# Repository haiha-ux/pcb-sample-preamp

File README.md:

# 2-channel phantom-powered mic preamp, KiCad sample

Owner: Hai (GitHub `haiha-ux`). This is a test and portfolio project, not client work.

A KiCad 10.0.6 project: schematic and a 2-layer 100 × 78 mm PCB, with ERC/DRC reports, fab outputs and renders. The audio signal path is routed by hand. Only power, the phantom feed and ground are autorouted. Every file is generated by the scripts in `tools/`, so the whole design can be rebuilt from scratch.

| Top copper | Bottom copper |
|---|---|
|  |  |

Schematic: [mic_preamp_2ch_schematic.pdf](mic_preamp_2ch_schematic.pdf)

## What is on the board

Per channel (×2):

| Block | Parts | Source |
|---|---|---|
| Input | Neutrik NC3FAH1 female XLR, horizontal (pin 1 GND, 2 hot, 3 cold) | — |
| Phantom feed | Per leg, **2 × 3.40 kΩ 0.1 % thin film 1206 in series (6.80 kΩ)**; 3-pin jumper ON (1-2 → +48 V) / OFF (2-3 → 47 kΩ to GND) | INA163 datasheet Fig. 5 (R1, R2, R3) |
| DC block | 2 × 47 µF 63 V **bi-polar** electrolytic | Fig. 5 note (1): non-polar required when phantom can be switched off |
| Input protection | BAV99 dual diode per leg, clamping to ±15 V | Fig. 5 text ("four diodes to the supplies") |
| Bias return | 2 × 2.2 kΩ **0.1 %** to GND | Fig. 5 (R4, R5) |
| Series resistor | 10 Ω 0.1 % per leg, between the clamp node and the IC input | design choice, see below |
| Preamp | TI **INA163UA** (SOIC-14), G = 1 + 6000/RG, RG = 60.4 Ω → G = 100.3 (40.0 dB) | gain equation and table, datasheet p. 6 |
| Decoupling | 100 nF X7R on each rail, right at the IC pins | Fig. 1 ("0.1 µF near the device pins") |

Shared: ±15 V header J3 with 10 µF on each rail and SMAJ16A TVS rail clamps (D21/D22);
+48 V header J4 with 47 µF/100 V + 100 nF; line-out header J5 (OUT1/GND/OUT2/GND); 4 × M3 holes.

I used the TI SBOS177D datasheet (INA163). The pin-out is from p. 2, the gain from p. 6 and the application circuit from Fig. 5 on p. 8. I rendered each figure and compared it to the schematic node by node (see the v2 correction below for why).

## Layout (v2)

The IC is rotated 90°. Input pins 4/5 face the XLR and output pins 8/9 face the connectors on the far edge, so the output never runs near the input, as the datasheet asks on p. 6.

The hot and cold legs are routed by hand as a symmetric pair. They run 11.5 mm apart, each straight through its DC-block capacitor and 10 Ω resistor. Clamp diodes and bias resistors branch off to the outside of each leg, and the two legs converge onto pins 4/5 at 45°. The measured copper length per leg after the capacitors is IN±_PROT 16.30 / 16.30 mm and IN± 11.72 / 11.72 mm, with 0 vias on each leg. Between the XLR and the capacitors the lengths differ: hot 24.8 mm, cold 19.5 mm, including the phantom stubs. The XLR pin order is mirrored relative to the IC pin order, so the legs must cross once. They cross here using the through-hole pads (hot on B.Cu), which needs no via.

The RG loop is short: R8/R18 sit next to the IC end, with a 9.1 mm loop (RG1A/RG1B).

Decoupling caps are placed on the V+ and V− pins, with a GND via at each cap. The Ref pin (pin 10) goes through a via straight into the GND pour, with no thermal relief. Datasheet p. 6 says even a few ohms in series with Ref hurts CMRR.

Freerouting 2.4.1 routes the ±15 V rails, the +48 V/phantom feed and GND. The 98 hand-routed tracks and vias are locked and exported as `fix`, so the router cannot move them. GND is poured on both layers, with 103 stitching vias.

## Outputs

| File | What |
|---|---|
| `mic_preamp_2ch.kicad_pro/.kicad_sch/.kicad_pcb/.kicad_dru` | KiCad project, including custom DRC rules |
| `lib/preamp.kicad_sym` | INA163UA symbol (not in the stock KiCad library) |
| `mic_preamp_2ch_schematic.pdf` | schematic, A3 |
| `reports/erc_report.rpt/.json` | raw `kicad-cli sch erc --severity-all` output |
| `reports/drc_report.rpt/.json` | raw `kicad-cli pcb drc --severity-all --schematic-parity` output |
| `fab/gerber/` + `fab/mic_preamp_2ch-gerber.zip` | Gerber X2 (9 layers), Excellon PTH/NPTH, drill maps, job file |
| `fab/mic_preamp_2ch-BOM.csv` | BOM with manufacturer, MPN, LCSC number |
| `fab/mic_preamp_2ch-CPL.csv` | pick-and-place (SMD only) |
| `renders/` | 3D top / bottom / iso, plus 2D copper views of top and bottom |

## Check results (final board)

ERC gives 0 errors and 0 warnings. DRC gives 0 errors, 0 unconnected and 0 schematic-parity issues, plus 4 warnings, all waived (see below).

The `kicad-cli` netlist is compared pin by pin with the intended net table (`tools/check_netlist.py`) and matches 100%. The check has a built-in sabotage case: moving one pin to another net must make it fail.

To confirm the 48 V clearance rule is applied, I raised it from 0.6 mm to 5 mm on a copy of the board. DRC then reported 301 "P48 creepage" violations, so the rule really matches the 48 V nets and does not pass trivially.

I counted the hits in the Excellon drill files (167 PTH + 8 NPTH), and they match the pads and vias on the board.

A separate reviewer re-ran the checks on another machine with KiCad 10.0.8 and the official libraries: ERC 0, DRC 0 errors, 0 unconnected, 0 parity issues, the same 4 XLR silk warnings, and no footprint differs from the library.

### Waived DRC items

| Item | Count | Reason |
|---|---|---|
| `silk_edge_clearance`, J1/J2 | 4 | The NC3FAH1 front flange sits in front of the panel line, which the footprint marks on Dwgs.User at x = 12.7 mm. The board edge is placed on that panel line, so the flange outline overhangs the board by design. |

### Design-rule decisions

These change what "0 errors" means.

- The board minimum track width is 0.15 mm (the KiCad default is 0.2 mm). This lets the autorouter narrow tracks at SOIC pads. JLCPCB and PCBWay handle 0.1 mm.
- ±15 V tracks are at least 0.4 mm. Inside the IC and decoupling-cap courtyards they may narrow to 0.3 mm. Those are local stubs carrying a few mA. This is the `Power neck-down` rule in the `.kicad_dru` file.
- All nets that can carry 48 V have at least 0.6 mm clearance: +48V, PH1/2, P1H/P1C/P2H/P2C, XLRx_HOT, XLRx_COLD and P48OFF1/2. The value is IPC-2221B table 6-1, column B2 (external, uncoated, 31-150 V). I did not count solder mask as a coating, which is the conservative choice.
- GND pads of J3/J4/J5 are solid, with no thermal relief. `tools/build_pcb.py::fix_starved` applies the same treatment to any GND pad that DRC reports as `starved_thermal`. There are none on the final board.

## v2 changes (after independent review of v1, commit efc1e58)

First, a correction. v1 had 47 Ω in series with each input, and the README said it came from datasheet Fig. 2. That was wrong. Fig. 2 shows 47 Ω in parallel with 1.2 µH, and I had read only the extracted text of the page, not the figure. Two 47 Ω resistors in series add √(4kT·94 Ω) ≈ 1.25 nV/√Hz, which is more than the INA163's own 1 nV/√Hz. v2 uses 10 Ω 0.1 % per leg. It still shares fault current with the IC's internal input clamps (abs-max 10 mA) and adds 0.57 nV/√Hz for both legs. The total is about 1.15 nV/√Hz, or +1.2 dB of noise.

Second, the parts are now matched for CMRR. The phantom feed resistors are 0.1 % thin film. A 6.81 kΩ part of that grade exists only in 1206 (0.25 W), but a shorted mic line puts 0.34 W into one leg. So each leg is 2 × 3.40 kΩ in series: 6.80 kΩ, 0.17 W per part. The bias resistors are 0.1 % too.

Third, the signal path is routed by hand (see Layout). In v1 everything was autorouted, so the hot and cold legs were not paired and there was a long detour.

Two items from the review are not done and remain known limitations:

- EMI filtering and AES48 grounding at the XLR. There are no small caps from pins 2/3 to the shell, and the shell is not taken to a separate chassis point. With the NC3FAH1 the shell is tied to pin 1 inside the connector. Separating them needs the NC3FAH2, which has its own ground contact.
- The DC servo of Fig. 5 (OPA134) is not fitted, so the output is DC-coupled. Estimated DC offset at G = 100, from datasheet values, is typically about 7 mV (Vos) plus 22 mV (Ios × 2.2 kΩ), and worst case about 30 mV plus 220 mV. The next stage must be AC-coupled.

## Deviations from the brief and datasheet

Please review these.

1. The phantom "switch" is a 3-pin jumper header (Molex 22-28-4030, 500 V) plus a shunt, not a slide switch. Every small PCB slide switch I checked has a DC rating below the 48 V ±4 V of IEC 61938:
   - C&K OS102011: 12 VDC
   - Würth 450301014042: 12 VDC
   - E-Switch EG1271: 30 V
   - E-Switch EG1224: 15 VDC
   - C&K 7101 toggle: 28 VDC

   The header doubles as the connection point for a panel-mount switch. Its OFF position discharges the node through 47 kΩ, the same as R3 in datasheet Fig. 5.
2. Gain is fixed at 40 dB, although the brief said "gain set by one resistor". Change R8/R18 using the RG table on p. 6.
3. The C1/C2 type (Nichicon UVP1J470MPD) is marked "Not For New Designs" on DigiKey. Cornell Dubilier 476BPS063M (active) is listed as the alternative. Neither is stocked at LCSC, so the board is not fully JLC-assemblable as is.
4. BAV99 is used instead of 1N4148, with the same function in a smaller package (Nexperia BAV99: 100 V, 4 A surge per the LCSC listing).

## Open questions

- XLR footprint. I used the stock KiCad `Jack_XLR_Neutrik_NC3FAH1_Horizontal`. The Neutrik/LCSC drawing download was blocked, so I did not check its hole sizes and peg positions against the manufacturer drawing myself. There is also no 3D model for it in the KiCad library.
- P48 hot-plug. A shorted XLR line dumps the 48 V charge of C1/C2 through the BAV99 diodes into the rails. I added the SMAJ16A rail clamps for that, but there is no surge simulation or test. The INA163 datasheet does not cover this case.
- Creepage value. I chose the conservative 0.6 mm. If solder mask is counted as a coating (IPC-2221B A6/B4), about 0.13 mm would be enough.
- Ground split by the rails and OUT1. The autorouted ±15 V rails and the OUT1 track run partly on B.Cu, under the channel-1 input area. They cut the bottom GND pour into a long slot (reviewer note). The F.Cu pour and the stitching vias carry the return current, but I have not analysed this. Planned for v3: move these tracks to the board edge or route them tighter, switch to the NC3FAH2 connector and add EMI filtering at the XLR.
- Footprint height for C1/C2. The bi-polar caps use `C_Radial_D10.0mm_H20.0mm_P5.00mm`, while the real part is 17.5 mm tall. The 2D land pattern is the same and only the 3D height is off.
- There is no SPICE or noise simulation. Gain, noise and offset come from the datasheet equations only.

## Tool chain and how to rebuild

The tool is KiCad 10.0.6. The schematic is written only through the Konnect MCP server (`tools/kcall.py` drives it over stdio), and the `.kicad_sch` file is never edited as text. The PCB is built with KiCad's own `pcbnew` Python API, including the hand-routed signal paths. The rest is routed with Freerouting 2.4.1 on Temurin JRE 25. The native `freerouting-cli` 2.5.0 crashed with a GraalVM serialization error. Parts and MPNs come from the JLCPCB/LCSC parts database (local copy), plus DigiKey lookups for the bi-polar caps and the switch ratings.

To rebuild:

```bash
python tools/build_schematic.py      # move the old .kicad_sch out of the way first
python tools/check_netlist.py
"C:/Program Files/KiCad/10.0/bin/python.exe" tools/build_pcb.py all   # with KiCad closed
bash tools/export_outputs.sh
```

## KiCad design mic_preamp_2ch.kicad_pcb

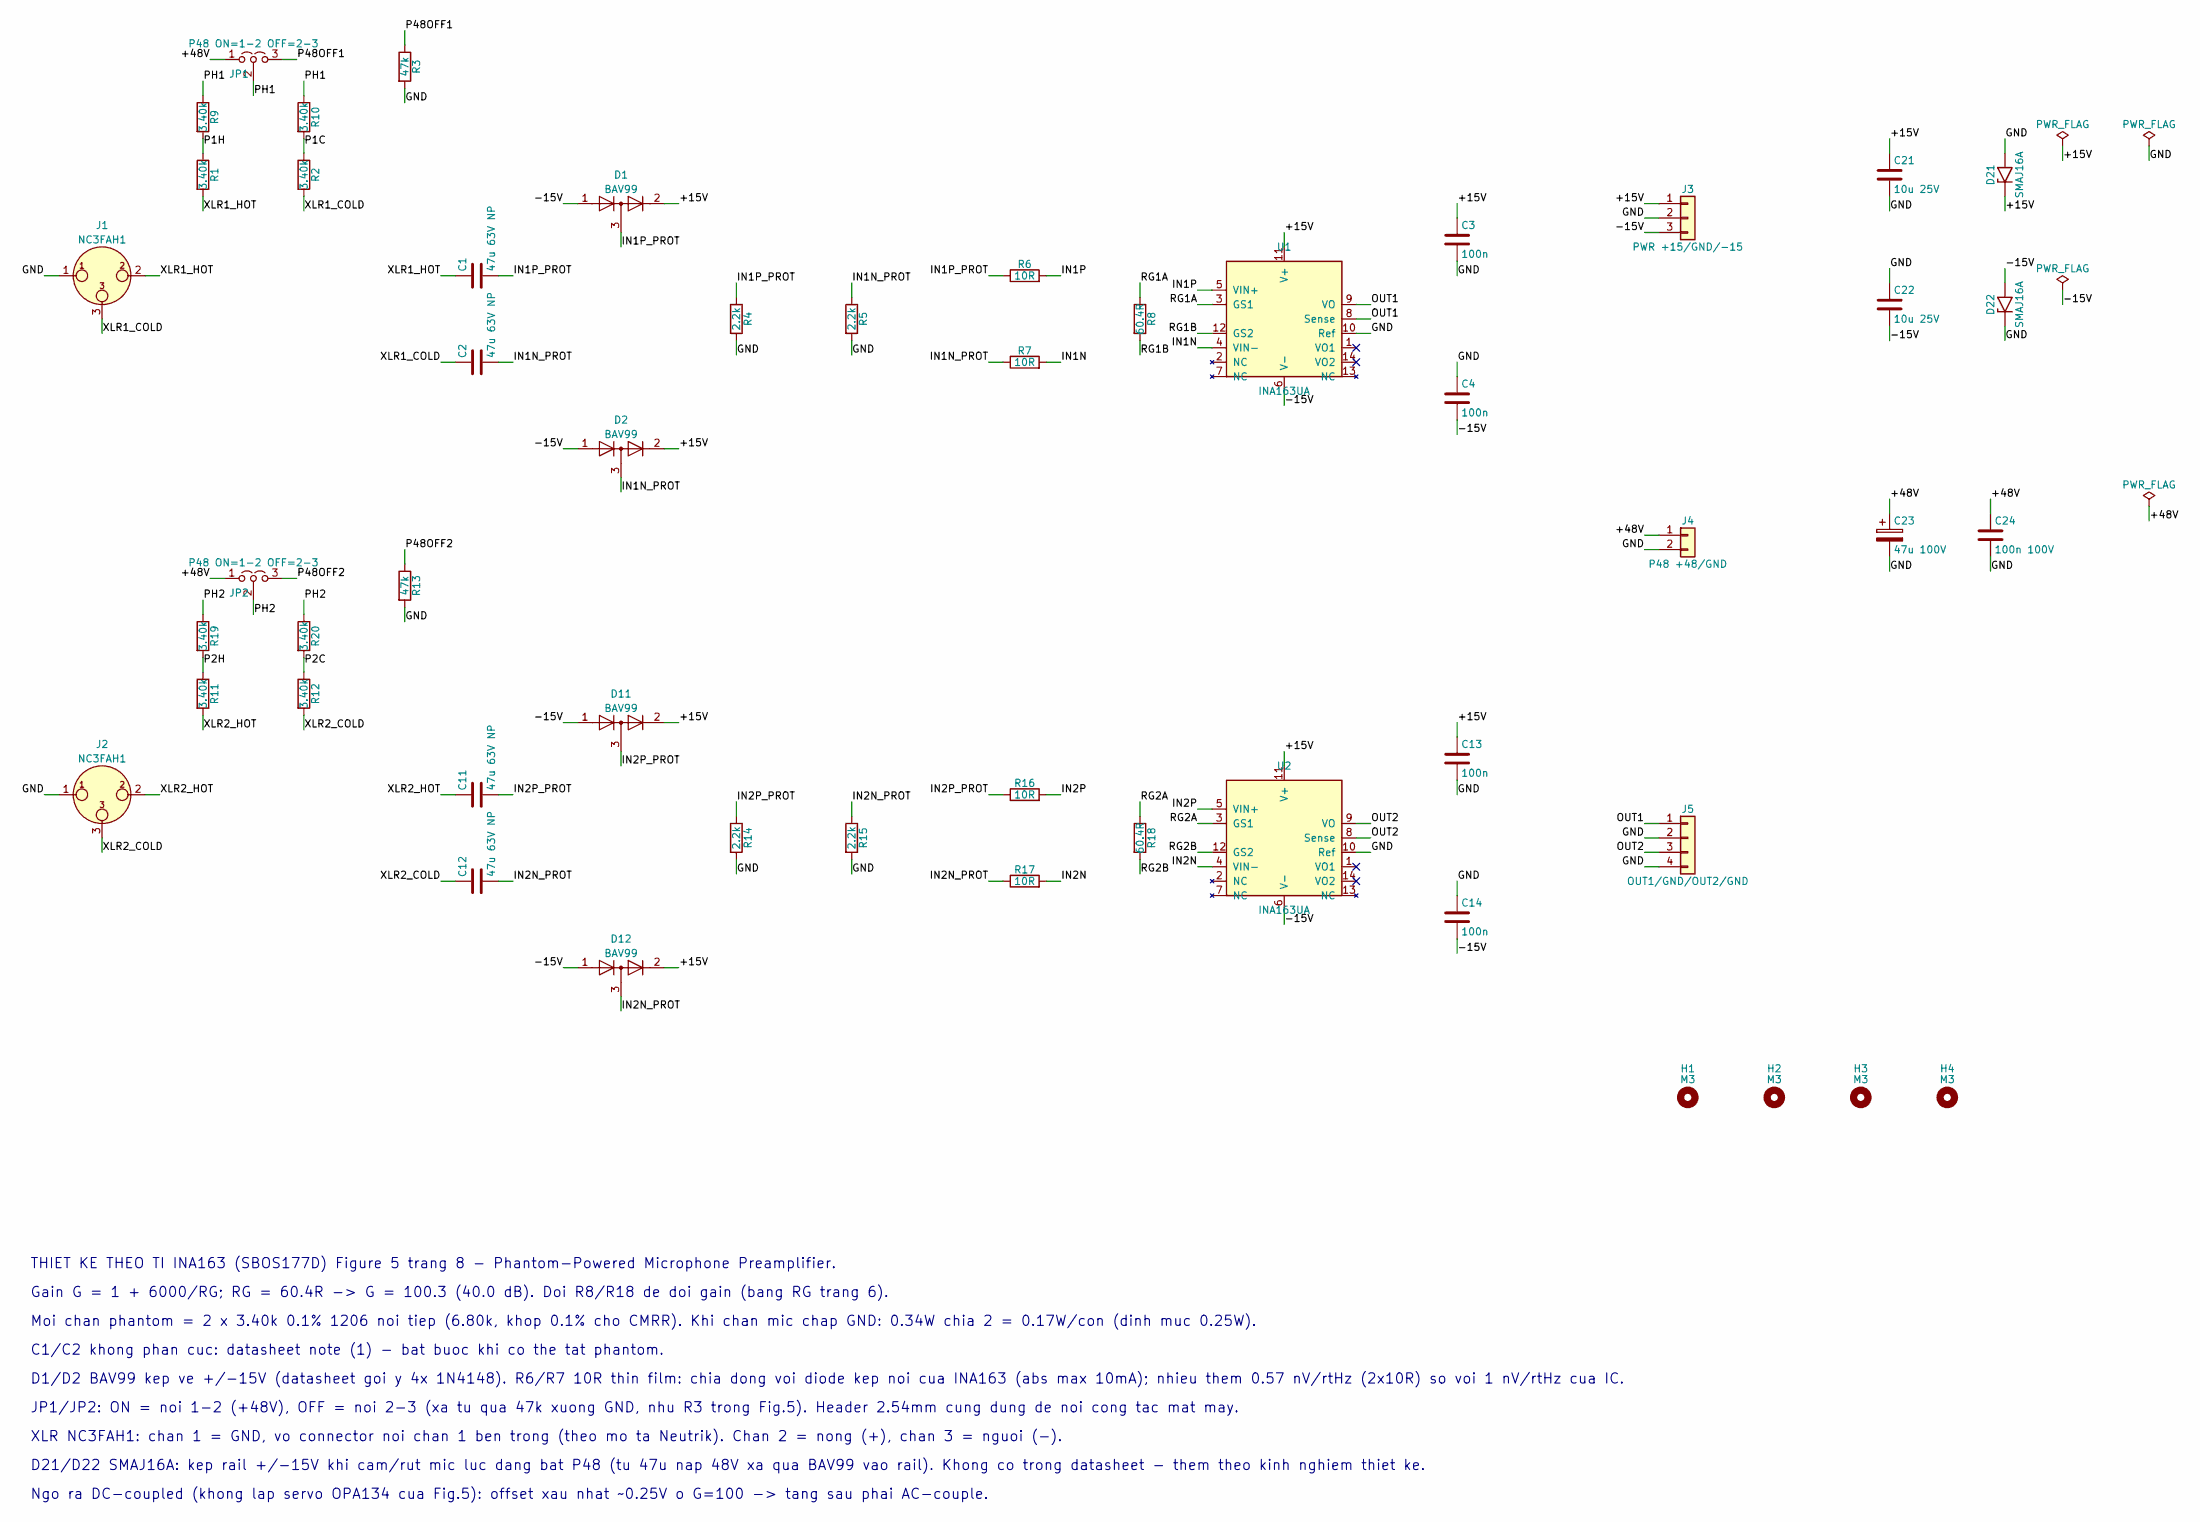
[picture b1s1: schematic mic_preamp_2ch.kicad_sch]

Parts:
C1, C2, C11, C12: 47u 63V NP; C_Radial_D10.0mm_H20.0mm_P5.00mm; MPN UVP1J470MPD; LCSC not stocked (DigiKey)
C3, C4, C13, C14: 100n; C_0805_2012Metric; MPN CC0805KRX7R9BB104; LCSC C49678
C21, C22: 10u 25V; C_1206_3216Metric; MPN CL31B106KAHNNNE; LCSC C14860
C23: 47u 100V; CP_Radial_D8.0mm_P3.50mm; MPN 4701010812R00; LCSC C5373423
C24: 100n 100V; C_0805_2012Metric; MPN CL21B104KCFNNNE; LCSC C28233
D1, D2, D11, D12: BAV99; SOT-23; MPN BAV99,215; LCSC C2500
D21, D22: SMAJ16A; D_SMA; MPN SMAJ16A; LCSC C74561
H1, H2, H3, H4: M3; MountingHole_3.2mm_M3
J1, J2: NC3FAH1; Jack_XLR_Neutrik_NC3FAH1_Horizontal; MPN NC3FAH1; LCSC C368476
J3: PWR +15/GND/-15; PinHeader_1x03_P2.54mm_Vertical; MPN 22284030; LCSC C587036
J4: P48 +48/GND; PinHeader_1x02_P2.54mm_Vertical; MPN 22284020; LCSC C234182
J5: OUT1/GND/OUT2/GND; PinHeader_1x04_P2.54mm_Vertical; MPN 22284040; LCSC C587039
JP1, JP2: P48 ON=1-2 OFF=2-3; PinHeader_1x03_P2.54mm_Vertical; MPN 22284030; LCSC C587036
R1, R2, R9, R10, R11, R12, R19, R20: 3.40k; R_1206_3216Metric; MPN RT1206BRD073K4L; LCSC C870711
R3, R13: 47k; R_0805_2012Metric; MPN 0805W8F4702T5E; LCSC C17713
R4, R5, R14, R15: 2.2k; R_0805_2012Metric; MPN RT0805BRD072K2L; LCSC C865371
R6, R7, R16, R17: 10R; R_0805_2012Metric; MPN CRF0805Q10R0BN; LCSC C55205321
R8, R18: 60.4R; R_0805_2012Metric; MPN FRC0805F60R4TS; LCSC C2933479
U1, U2: INA163UA; SOIC-14_3.9x8.7mm_P1.27mm; MPN INA163UA; LCSC C2868965

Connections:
/+15V: C3.1, C13.1, C21.1, D1.2 (A), D2.2 (A), D11.2 (A), D12.2 (A), D21.1 (A1), J3.1, U1.11 (V+), U2.11 (V+)
/+48V: C23.1, C24.1, J4.1, JP1.1 (A), JP2.1 (A)
/-15V: C4.2, C14.2, C22.2, D1.1 (K), D2.1 (K), D11.1 (K), D12.1 (K), D22.2 (A2), J3.3, U1.6 (V-), U2.6 (V-)
/GND: C3.2, C4.1, C13.2, C14.1, C21.2, C22.1, C23.2, C24.2, D21.2 (A2), D22.1 (A1), J1.1, J2.1, J3.2, J4.2, J5.2, J5.4, R3.2, R4.2, R5.2, R13.2, R14.2, R15.2, U1.10 (Ref), U2.10 (Ref)
/IN1N: R7.2, U1.4 (VIN-)
/IN1N_PROT: C2.2, D2.3 (K), R5.1, R7.1
/IN1P: R6.2, U1.5 (VIN+)
/IN1P_PROT: C1.2, D1.3 (K), R4.1, R6.1
/IN2N: R17.2, U2.4 (VIN-)
/IN2N_PROT: C12.2, D12.3 (K), R15.1, R17.1
/IN2P: R16.2, U2.5 (VIN+)
/IN2P_PROT: C11.2, D11.3 (K), R14.1, R16.1
/OUT1: J5.1, U1.8 (Sense), U1.9 (VO)
/OUT2: J5.3, U2.8 (Sense), U2.9 (VO)
/P1C: R2.1, R10.2
/P1H: R1.1, R9.2
/P2C: R12.1, R20.2
/P2H: R11.1, R19.2
/P48OFF1: JP1.3 (B), R3.1
/P48OFF2: JP2.3 (B), R13.1
/PH1: JP1.2 (C), R9.1, R10.1
/PH2: JP2.2 (C), R19.1, R20.1
/RG1A: R8.1, U1.3 (GS1)
/RG1B: R8.2, U1.12 (GS2)
/RG2A: R18.1, U2.3 (GS1)
/RG2B: R18.2, U2.12 (GS2)
/XLR1_COLD: C2.1, J1.3, R2.2
/XLR1_HOT: C1.1, J1.2, R1.2
/XLR2_COLD: C12.1, J2.3, R12.2
/XLR2_HOT: C11.1, J2.2, R11.2

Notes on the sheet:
THIET KE THEO TI INA163 (SBOS177D) Figure 5 trang 8 - Phantom-Powered Microphone Preamplifier.
Gain G = 1 + 6000/RG; RG = 60.4R -> G = 100.3 (40.0 dB). Doi R8/R18 de doi gain (bang RG trang 6).
Moi chan phantom = 2 x 3.40k 0.1% 1206 noi tiep (6.80k, khop 0.1% cho CMRR). Khi chan mic chap GND: 0.34W chia 2 = 0.17W/con (dinh muc 0.25W).
C1/C2 khong phan cuc: datasheet note (1) - bat buoc khi co the tat phantom.
D1/D2 BAV99 kep ve +/-15V (datasheet goi y 4x 1N4148). R6/R7 10R thin film: chia dong voi diode kep noi cua INA163 (abs max 10mA); nhieu them 0.57 nV/rtHz (2x10R) so voi 1 nV/rtHz cua IC.
JP1/JP2: ON = noi 1-2 (+48V), OFF = noi 2-3 (xa tu qua 47k xuong GND, nhu R3 trong Fig.5). Header 2.54mm cung dung de noi cong tac mat may.
XLR NC3FAH1: chan 1 = GND, vo connector noi chan 1 ben trong (theo mo ta Neutrik). Chan 2 = nong (+), chan 3 = nguoi (-).
D21/D22 SMAJ16A: kep rail +/-15V khi cam/rut mic luc dang bat P48 (tu 47u nap 48V xa qua BAV99 vao rail). Khong co trong datasheet - them theo kinh nghiem thiet ke.
Ngo ra DC-coupled (khong lap servo OPA134 cua Fig.5): offset xau nhat ~0.25V o G=100 -> tang sau phai AC-couple.

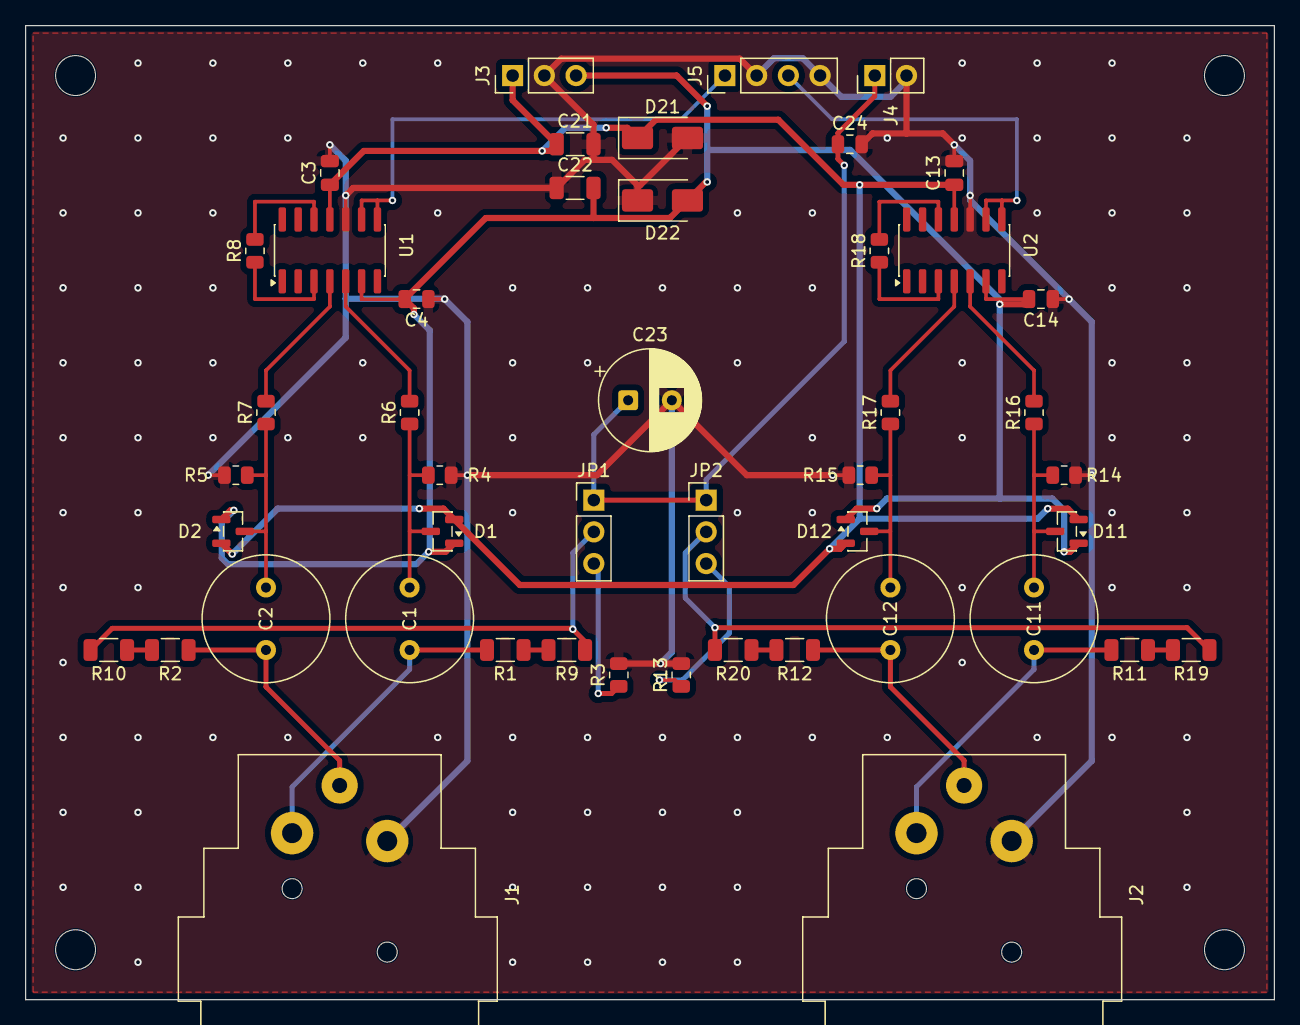
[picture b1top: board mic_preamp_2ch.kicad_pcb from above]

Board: 2 copper layers, 100.0 x 78.0 mm, 51 parts (0 on the bottom side), 30 nets.

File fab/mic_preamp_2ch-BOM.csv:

"Designator","Value","Footprint","Manufacturer","MPN","LCSC","Spec","Qty"
"C1,C2,C11,C12","47u 63V NP","Capacitor_THT:C_Radial_D10.0mm_H20.0mm_P5.00mm","Nichicon","UVP1J470MPD","not stocked (DigiKey)","47uF 63V bi-polar D10x17.5 P5.0; alt Cornell Dubilier 476BPS063M","4"
"C3,C4,C13,C14","100n","Capacitor_SMD:C_0805_2012Metric","YAGEO","CC0805KRX7R9BB104","C49678","100nF 50V X7R 0805","4"
"C21,C22","10u 25V","Capacitor_SMD:C_1206_3216Metric","Samsung Electro-Mechanics","CL31B106KAHNNNE","C14860","10uF 25V X7R 1206","2"
"C23","47u 100V","Capacitor_THT:CP_Radial_D8.0mm_P3.50mm","NJCON","4701010812R00","C5373423","47uF 100V D8x12 P3.5","1"
"C24","100n 100V","Capacitor_SMD:C_0805_2012Metric","Samsung Electro-Mechanics","CL21B104KCFNNNE","C28233","100nF 100V X7R 0805","1"
"D1,D2,D11,D12","BAV99","Package_TO_SOT_SMD:SOT-23","Nexperia","BAV99,215","C2500","","4"
"D21,D22","SMAJ16A","Diode_SMD:D_SMA","Littelfuse","SMAJ16A","C74561","TVS 16V standoff, 26V clamp, 400W, rail clamp for P48 hot-plug","2"
"H1-H4","M3","MountingHole:MountingHole_3.2mm_M3","","","","","4"
"J1,J2","NC3FAH1","Connector_Audio:Jack_XLR_Neutrik_NC3FAH1_Horizontal","Neutrik","NC3FAH1","C368476","","2"
"J3","PWR +15/GND/-15","Connector_PinHeader_2.54mm:PinHeader_1x03_P2.54mm_Vertical","Molex","22284030","C587036","","1"
"J4","P48 +48/GND","Connector_PinHeader_2.54mm:PinHeader_1x02_P2.54mm_Vertical","Molex","22284020","C234182","","1"
"J5","OUT1/GND/OUT2/GND","Connector_PinHeader_2.54mm:PinHeader_1x04_P2.54mm_Vertical","Molex","22284040","C587039","","1"
"JP1,JP2","P48 ON=1-2 OFF=2-3","Connector_PinHeader_2.54mm:PinHeader_1x03_P2.54mm_Vertical","Molex","22284030","C587036","1x3 2.54mm 500V + shunt Sullins SPC02SYAN (LCSC C6297395)","2"
"R1,R2,R9-R12,R19,R20","3.40k","Resistor_SMD:R_1206_3216Metric","YAGEO","RT1206BRD073K4L","C870711","3.40k 0.1% 25ppm thin film 1206 0.25W 200V; 2 in series per leg = 6.80k","8"
"R3,R13","47k","Resistor_SMD:R_0805_2012Metric","UNI-ROYAL","0805W8F4702T5E","C17713","47k 1% 0805 150V","2"
"R4,R5,R14,R15","2.2k","Resistor_SMD:R_0805_2012Metric","YAGEO","RT0805BRD072K2L","C865371","2.2k 0.1% 25ppm thin film 0805","4"
"R6,R7,R16,R17","10R","Resistor_SMD:R_0805_2012Metric","SIE","CRF0805Q10R0BN","C55205321","10R 0.1% thin film 0805","4"
"R8,R18","60.4R","Resistor_SMD:R_0805_2012Metric","FOJAN","FRC0805F60R4TS","C2933479","60.4R 1% 0805 (G=100)","2"
"U1,U2","INA163UA","Package_SO:SOIC-14_3.9x8.7mm_P1.27mm","Texas Instruments","INA163UA","C2868965","","2"

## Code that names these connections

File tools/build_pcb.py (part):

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FR_JAR = r"C:\Users\USER\Documents\KiCad\10.0\3rdparty\plugins\app_freerouting_kicad-plugin\jar\freerouting-2.4.1.jar"
mm = pcbnew.FromMM

HV_NETS = ["+48V", "PH1", "PH2", "XLR1_HOT", "XLR1_COLD", "XLR2_HOT", "XLR2_COLD", "P48OFF1", "P48OFF2",
           "P1H", "P1C", "P2H", "P2C"]
POWER_NETS = ["GND", "+15V", "-15V"]

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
